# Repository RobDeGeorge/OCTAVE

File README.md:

<div align="center">

# OCTAVE

### **O**pen-source **C**ross-platform **T**elematics for **A**ugmented **V**ehicle **E**xperience

<sub>The real app, shot from a script: a real phone mirrored live (street names made up), engine data from the built-in car simulator.</sub>

**Windows · macOS · Linux · Raspberry Pi / Orange Pi · Android · your browser**

**Try it in your browser: https://robdegeorge.com/OCTAVE/** (the simulated car, no install, about 25 MB)

### [Download](https://github.com/RobDeGeorge/OCTAVE/releases/latest) &nbsp;·&nbsp; [Wiki](https://robdegeorge.com/OCTAVE/wiki/) &nbsp;·&nbsp; [Build your own frontend](https://robdegeorge.com/OCTAVE/wiki/writing-a-frontend.html) &nbsp;·&nbsp; [Frontend playground](https://robdegeorge.com/OCTAVE/playground.html)

</div>

---

**OCTAVE is a car head unit you build yourself**, on a Pi behind the dash, a laptop or an old Android tablet. Your phone, your music and the car's own data on one screen, and every pixel yours to change. I daily-drive it in my 2003 Jeep TJ.

> **Getting data from your car:** plug a $15–30 ELM327 OBD-II adapter into the port under your dash (every US car since 1996 has one). USB works everywhere; Bluetooth pairs inside OCTAVE on Linux and the Pi, and through system settings on Windows and macOS; BLE works on Android.
>
> No car handy? `octave --sim` drives a simulated one, in any build.

<table>
<tr>
<td width="33%" align="center"><br><b>Your phone on the dash</b><br><sub>Android by cable or Wi-Fi, iPhone over AirPlay</sub></td>
<td width="33%" align="center"><br><b>Music paints the dash</b><br><sub>Every song recolours the UI</sub></td>
<td width="33%" align="center"><br><b>A Home that is yours</b><br><sub>Pick one, or write your own</sub></td>
</tr>
<tr>
<td align="center"><br><b>A black box</b><br><sub>Every drive recorded</sub></td>
<td align="center"><br><b>Shift light & codes</b><br><sub>Read and clear the check-engine light</sub></td>
<td align="center"><br><b>Open API</b><br><sub>Drive it from a browser or a script</sub></td>
</tr>
<tr>
<td align="center"><br><b>Your car in 3D</b><br><sub>The Jeep, a BMW, or a model of your own</sub></td>
<td align="center"><br><b>Your own screen</b><br><sub>Swap the whole UI for one you wrote</sub></td>
<td align="center"><br><b>Its own hardware</b><br><sub>Designed here, not built yet</sub></td>
</tr>
</table>

---

## Your phone on the dash

Plug in an Android phone and it is on the dash: in the middle of Home, or in place of the album art. **Nothing to install on the phone**, only USB debugging turned on.

- **Pull the cable and it carries on** over Wi-Fi (Android 11+), song and all.
- **Touch it on the dash**, and the dash's play, skip and volume drive the phone's player.

**iPhone:** OCTAVE is an AirPlay receiver, and pairs as a Bluetooth mouse so taps on the dash reach the phone. Linux and the Pi for now.

**Android Auto** runs through Google's Desktop Head Unit or OCTAVE's own receiver (beta).

## Music that paints the whole dash

Every song recolours the whole interface from its cover. Tap the art to play it on something else: a spinning vinyl, or one of five 3D players, from a record player to an iPod. Local MP3, M4A and FLAC.

## A Home that is yours

<p align="center"><sub>Cockpit, Glass, Trail, Retro, Rings, Telemetry: the same car, the same minute.</sub></p>

Pick your Home in Settings: six screens built by hand, each its own idea of a dash, or the phone-in-the-middle one at the top of this page.

Or write your own. A dashboard is a small JSON file: a grid of **16 widget types** bound to any of **129 live readings** ([format](docs/GAUGE_AUTHORING.md)). Drop it in the dashboards folder and it appears. Or build it in a browser, previewed live on the car's screen:

Every reading your car reports is one tap away as plain cards, and every page re-flows for an upright screen.

<p align="center">
  
  &nbsp;

</p>

## A black box for every drive

OCTAVE records **every reading of every drive** in the background. Trip History charts any of them over a whole trip and exports CSV.

**Trends** compares your drives: warm-up time, coolant, voltage, idle, fuel trims. When recent drives drift it says so, and what usually causes it. Here a thermostat is starting to stick open.

<sub>The history in these pictures is generated: 40 drives with a thermostat wearing out.</sub>

## Shift light, warnings and trouble codes

Set your own RPM bands: green, flashing yellow, then **the whole screen strobes red**, whatever page you're on.

Check-engine light on? Read the codes in plain English and clear them from the dash.

## Your car, live in 3D

An inclinometer: your vehicle over a level ring, tilted in real time by an IMU on the dash. A rigged Jeep TJ and a BMW 330i ZHP ship with it, or add a model of your own car (any `.glb`, [guide](docs/VEHICLES.md)).

Pitch, roll, heading, G-force, altitude and temperature, sampled at 200 Hz.

## Drive it from anything

<table>
<tr>
<td width="38%" align="center"></td>
<td>

Everything the touch screen can do is open to other programs over a small JSON API. Start OCTAVE with `--service --service-bind 0.0.0.0` and open **`http://<head-unit-ip>:9876/`** on your phone, or run it with **no screen at all** (`--headless`) and make your own UI.

```python
from octave_client import Client

with Client() as octave:
    octave.call("nowPlaying", "next")
    octave.subscribe("paramStore", properties=["RPM", "SPEED"])
    for event in octave.events():
        print(event["values"])        # {'RPM': 2210, 'SPEED': 41}
```

[SDKs](sdk/) for Python, TypeScript and Go, [starter projects](templates/), the [API reference](https://robdegeorge.com/OCTAVE/wiki/api-reference.html), and a walkthrough: **[Writing a Frontend](https://robdegeorge.com/OCTAVE/wiki/writing-a-frontend.html)**. Install yours as the head unit's screen from Settings; five presses of mute always bring the built-in one back.

**[Try a frontend in your browser](https://robdegeorge.com/OCTAVE/playground.html)**, or browse the **[gallery](https://robdegeorge.com/OCTAVE/wiki/frontend-gallery.html)** of five complete examples (`examples/frontends/`, MIT).

</td>
</tr>
</table>

<p align="center"><sub>Glass (Svelte), Sunlight (Go), Retro Cluster (Rust), Arcade (C + SDL2), Console (Python): five complete screens for the same car.</sub></p>

## Hardware designed here

The $20 ELM327 clones work, and they are the slow part of the system. So OCTAVE is getting hardware of its own, designed in this repository as code: [`hardware/`](hardware/).

- **OBD adapter:** every OBD-II bus on one 80 x 55 mm board (two CAN, K-line, J1850 VPW / PWM for older cars like my TJ), an STM32 on the car's side, an ESP32 for Bluetooth and Wi-Fi, USB-C.
- **LoRa pod:** where the parked car is, beaconed over LoRa where there is no phone signal ([plan](TODO/lora-car-finder.md)).
- **Volume knob:** wireless, battery-powered, with a ring of twelve LEDs that follows the theme.

> **Where it stands:** all three boards are designed and routed. **Nobody else has reviewed them, and none has been ordered or built.** Read them, tell me what is wrong with them, but do not send them to a fab yet ([plan](TODO/diy-obd-adapter.md)). Nothing in OCTAVE depends on them.

---

## Install

Grab the file for your platform from **[Releases](https://github.com/RobDeGeorge/OCTAVE/releases/latest)**. No toolchain needed.

| Platform | File | |
|---|---|---|
| Windows | `OCTAVE-<version>-windows-x86_64.exe` | Run the installer |
| macOS | `OCTAVE-<version>-macos.dmg` | Drag to Applications |
| Linux | `OCTAVE-<version>-linux-x86_64.AppImage` | `chmod +x`, then run |
| Raspberry Pi / Orange Pi (64-bit) | `OCTAVE-<version>-linux-aarch64.AppImage` | `chmod +x`, then run |
| Android | `OCTAVE-<version>-android-arm64-v8a.apk` | Sideload it |

<details>
<summary>Platform notes</summary>

- **Linux:** Ubuntu 22.04+, Debian, Mint, Fedora, openSUSE and Arch. Arch may need `sudo pacman -S fuse2`, or run `./OCTAVE-*.AppImage --appimage-extract-and-run`.
- **Android:** releases from 0.9.4 on share one signing key and update in place. Coming from 0.9.3 or older, uninstall the old version first.

</details>

## How it compares

| | OCTAVE | Crankshaft | OpenAuto Pro | Stock Android Auto |
|---|---|---|---|---|
| Open source | Yes, GPLv3 | Yes | partial | No |
| Works without a phone | Yes | No, AA projection | No, AA projection | No |
| Live OBD-II, your own dashboards | Yes | No | limited | No |
| Records every drive | Yes | No | No | No |
| Phone mirroring | Yes: Android with nothing to install, iPhone over AirPlay | AA only | AA only | n/a |
| Open API for your own UI | Yes | No | No | No |
| Fully themable / forkable UI | Yes, QML | limited | limited | No |
| Develop on your laptop | Yes, Win / macOS / Linux | Pi only | Pi only | n/a |

## Everything else it does

- **Swipe between sections**: a sideways flick on any page opens the next one
- **ESP32 wireless volume knob** with an LED ring that matches the theme
- **Gesture sensor** (PAJ7620U2): wave to skip, pause or change the volume
- **Bluetooth OBD adapters** found, paired and connected from the app on Linux; BLE adapters on Android
- **Readings your car's maker kept to itself**: describe a manufacturer-specific PID in a file and it becomes a gauge like any other ([guide](docs/CUSTOM_PIDS.md))
- **A bus monitor**: watch and record the raw messages on the vehicle bus, listen only ([guide](docs/BUS_MONITOR.md))
- **Spotify** (experimental): your playlists in the same song table as your own music, playing on the Spotify app on your phone (Premium)
- **Pick the audio output**: the car's amp, a USB DAC or Bluetooth, from Settings
- **The browser demo is the real app**: point it at a folder of your own music, or connect a real adapter from Chrome or Edge, Bluetooth LE or on a USB cable
- **100+ settings**, all on the screen, all saved
- **The whole wiki inside the app**, readable offline
- **Logs and crash traces** you can export from the dash when something goes wrong

---

## Hack on it

OCTAVE is C++ / Qt 6 with a QML frontend, built with CMake, small enough to fork. `--dev` runs it with a **simulated car** (warm-up, overheating and low-fuel scenarios) and simulated motion, so you can work on gauges at your desk.

<details>
<summary><b>Build from source</b></summary>

Qt 6.7+ and CMake 3.21+:

```bash
git clone https://github.com/RobDeGeorge/OCTAVE.git
cd OCTAVE
cmake -S . -B build -DCMAKE_BUILD_TYPE=Debug
cmake --build build -j8
./build/octave --dev                       # with the simulated car
ctest --test-dir build --output-on-failure # the test suite
```

Every platform and packaging target is in [BUILD.md](BUILD.md). The optional Python tools around the app (dev scripts, docs builders) install into a virtualenv next to the checkout:

```bash
python3 -m venv venv && venv/bin/pip install -r requirements.txt
```

Until October 2026 OCTAVE also had a Python / PySide6 backend. It is frozen, with its own wiki, on the [`python-final`](https://github.com/RobDeGeorge/OCTAVE/tree/python-final) branch.

</details>

<details>
<summary><b>Dev tooling: how the clips above were made</b></summary>

Every clip and picture in this README is scripted, and one command makes them all again. `./build/octave --dev --profile` (a Debug build) runs OCTAVE with the simulator and a local command server; a story script drives it scene by scene (navigate, play, floor the throttle, tap buttons by their label, type into fields), captures the window from inside Qt, and writes WebP and PNG. The same run fills the black box with two months of mock drives, shoots the browser pages in headless Chromium, renders the boards with `kicad-cli` from the committed design, and then checks that every picture this file points at exists. The same channel is exposed as MCP tools, so a coding agent can drive the app, change settings, read performance counters and record clips. The in-app half is in `src/dev/`; see the [Development guide](https://robdegeorge.com/OCTAVE/wiki/development.html).

</details>

## What's next

- **The OBD adapter and the pods as real boards**: a review, a first order, and firmware on hardware ([plan](TODO/diy-obd-adapter.md))
- **Android on the Play Store**: the APK runs today as a sideload ([plan](TODO/android-cpp-port.md))
- **Wireless CarPlay / Android Auto** through a CarlinKit dongle ([plan](TODO/carlinkit-dongle-port.md))
- **Video over the API**, so your own frontend can show the phone mirror too ([plan](TODO/open-backend.md))

Every plan lives in [`TODO/`](TODO/).

## Documentation

The **[wiki](https://robdegeorge.com/OCTAVE/wiki/)** covers the architecture, every manager and page, every setting, hardware setup and the build guides. The same pages ship in [`wiki/`](wiki/index.html) and inside the app. Building gauges: [`docs/GAUGE_AUTHORING.md`](docs/GAUGE_AUTHORING.md). Building a frontend: [Writing a Frontend](https://robdegeorge.com/OCTAVE/wiki/writing-a-frontend.html) and [`docs/api/`](docs/api/README.md).

## Contributing

Pull requests and bug reports are welcome. Built a dashboard, a sensor integration, a port to new hardware, or your own frontend? Open an issue or a PR. I'd love to see it.

<details>
<summary><b>Built with</b></summary>

OCTAVE stands on a lot of other people's work.

**C++ app (every release binary)**

| Library | Used for |
|---|---|
| [Qt 6](https://www.qt.io/) (Core, Gui, Qml, Quick, Quick Controls 2, Multimedia, Network, Concurrent, SerialPort, Bluetooth) | The whole application: UI, audio playback, networking, serial and Bluetooth OBD |
| Qt Quick 3D, Quick 3D Asset Utils, Quick Timeline | The 3D Jeep and the music-device scenes |
| Qt DBus | BlueZ pairing on Linux |
| Qt Sensors | The phone's motion sensors on Android |
| [TagLib](https://taglib.org/) | Reading tags and embedded album art |
| [FFmpeg](https://ffmpeg.org/) (libavcodec, libavutil) | Decoding the phone mirror's H.264 stream |
| [SQLite](https://sqlite.org/) | The black box (compiled in from `third_party/sqlite/`) |
| [OpenSSL](https://www.openssl.org/) | The built-in Android Auto receiver's encryption; the AirPlay receiver |
| [libplist](https://libimobiledevice.org/) | The AirPlay receiver (Linux), with FFmpeg and OpenSSL |
| [CMake](https://cmake.org/) | Build system |

**Python helper tools (optional, `requirements.txt`)**

| Package | Used for |
|---|---|
| [MCP Python SDK](https://github.com/modelcontextprotocol/python-sdk), [Pillow](https://python-pillow.org/), [mss](https://github.com/BoboTiG/python-mss), [NumPy](https://numpy.org/), [psutil](https://github.com/giampaolo/psutil) | Dev tooling: MCP servers, screenshots and clips, perf scripts |
| [python-OBD](https://github.com/brendan-w/python-OBD) | Dev scripts for reading and clearing trouble codes |
| [Ruff](https://docs.astral.sh/ruff/) | Lint |

**Android**

| Library | Used for |
|---|---|
| Qt for Android, Gradle, Android SDK / NDK | Building the APK |
| [OpenSSL](https://www.openssl.org/) | HTTPS for Qt Network (`android/openssl/`) |

**Code bundled in this repository**

| Component | License | Where |
|---|---|---|
| [scrcpy](https://github.com/Genymobile/scrcpy) server, forked at v3.3.4 | Apache 2.0 | `phone_server/`, prebuilt jar in `tools/phone-server/` |
| [UxPlay](https://github.com/FDH2/UxPlay)'s AirPlay library, 1.74 | LGPL 2.1+, with GPL 3.0 and MIT parts (see its README) | `third_party/uxplay/` |
| [QR Code generator library](https://www.nayuki.io/page/qr-code-generator-library) by Project Nayuki | MIT | `src/phone_mirror/qrcodegen.*` |
| Android platform-tools (`adb`) | See its `NOTICE.txt` | `tools/platform-tools/` |

**External tools and services:** adb (phone mirroring and Android Auto), Google's Android Auto Desktop Head Unit (the Android Auto view).

**The boards (`hardware/`):** [KiCad](https://www.kicad.org/) (the project, `kicad-cli` checks, fab output and the renders above), [Freerouting](https://github.com/freerouting/freerouting) (autorouting), [ngspice](https://ngspice.sourceforge.io/) (simulations), `arm-none-eabi-gcc` (firmware).

**Fonts, icons and 3D assets**

- **[Google Sans](https://fonts.google.com/)**: UI typeface. **[JetBrains Mono](https://www.jetbrains.com/lp/mono/)**: monospace readouts.
- **OCTAVE Symbols**: a subset of [Noto Sans Symbols and Noto Sans Symbols 2](https://fonts.google.com/noto) (SIL OFL), renamed as the OFL requires, built by `tools/fonts/build_symbol_font.py` with [fontTools](https://github.com/fonttools/fonttools).
- **Icons**: original SVGs drawn for OCTAVE (Illustrator sources in `frontend/assets/-src/`).
- **The 2003 Jeep TJ**: an original model, built procedurally in [Blender](https://www.blender.org/) by `tools/vehicle/build_jeep_tj.py` from photos of one real TJ; no third-party meshes or textures ([details](tools/vehicle/README.md)).
- **Record player, cassette deck, CD player, iPod and friends**: original glTF models generated by `tools/music_devices/generate.py` (NumPy, Pillow).
- **Studio lighting (`.hdr`)**: generated by `tools/vehicle/build_studio_probe.py`.

**CI and packaging:** [GitHub Actions](https://github.com/features/actions) with [install-qt-action](https://github.com/jurplel/install-qt-action), [setup-android](https://github.com/android-actions/setup-android) and [action-gh-release](https://github.com/softprops/action-gh-release); [vcpkg](https://vcpkg.io/) and [Homebrew](https://brew.sh/) for TagLib and FFmpeg; [Inno Setup](https://jrsoftware.org/isinfo.php) for the Windows installer; [linuxdeploy](https://github.com/linuxdeploy/linuxdeploy) with its Qt plugin for the AppImages; `windeployqt`, `macdeployqt` and `androiddeployqt` from Qt.

</details>

## License

Copyright 2026 Rob DeGeorge.

OCTAVE is free software: you can redistribute it and/or modify it under the terms of the GNU General Public License as published by the Free Software Foundation, either version 3 of the License, or (at your option) any later version. It is distributed in the hope that it will be useful, but WITHOUT ANY WARRANTY; without even the implied warranty of MERCHANTABILITY or FITNESS FOR A PARTICULAR PURPOSE. See [LICENSE](LICENSE) for the full text.

The service clients (`sdk/`), starter projects (`templates/`) and example frontends (`examples/frontends/`) are MIT, so a frontend you build on them can use any license ([Your Frontend, Your License](wiki/writing-a-frontend.html#license)).

Code published before 2026-10-12 (v0.9.4 and earlier) was released under the MIT License and remains available under those terms.

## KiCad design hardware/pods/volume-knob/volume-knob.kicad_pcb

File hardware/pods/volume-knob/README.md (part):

# OCTAVE wireless volume knob, Rev 0

A battery-powered knob for OCTAVE's volume: an ESP32-C3, a rotary encoder with a push switch, a ring of 12 addressable RGB LEDs and a rechargeable cell on a 47 mm round board. It talks ESP-NOW to the ESP32-S3 USB dongle OCTAVE already supports (`src/managers/esp32volumemanager.cpp`: `+N` / `-N` / `M` lines one way, volume, mute and colour the other), so the app needs no change. It is an OCTAVE pod (`../README.md`) on the radio link. Built for a Jeep parked in Arizona: every part is rated to 80 C or more.

**Status:** generated, routed and checked by rule (ERC 0 errors, DRC 0 clearance errors, 0 unconnected, schematic and board agree), by two datasheet audits of the netlist, one review of the circuit and one of the routed layout, whose findings are fixed (see "What the reviews changed"). A third audit (five independent reviews against the makers' datasheets: pin numbers and land patterns, the power chain, the module and what firmware needs of it, the manufacturing files, the routed copper and the mechanics) found no wrong pin, footprint or rotation; what it changed is in the same section, and those last changes are themselves unreviewed. Not reviewed by a person, not ordered, no firmware. Read "Before ordering".

## What is on it

| Block | Part | Why this one |
|---|---|---|
| Cell | Nichicon SLB12400H1311CX, lithium titanate, 2.1 V 130 mAh, 12.5 x 40 mm | The only small rechargeable found that is rated for a hot car: -30 to 80 C, no thermal runaway, 20,000 cycles. A LiPo is rated to 60 C at best. Hand-fitted (not an LCSC part) |
| Charger | TI BQ25173-Q1, linear, set to 2.40 V and 150 mA | A charger whose voltage can be set under the cell's 2.5 V limit. About an hour for a full charge |
| Cut-off | TI TPS3840PL16 on the boost's enable | Stops the discharge at 1.6 V, back on at 1.7 V. The cell is rated to 1.5 V and rests at 1.98 V when empty, so only load on an empty cell trips it. The 1.8 V PL18 was the first choice: none in stock |
| 3.3 V | TI TPS61299 boost, 95 nA quiescent | The knob sleeps nearly all its life |
| Reset | TI TPS3840DL28 on the module's EN | The rail rises and falls slowly with the cell |
| MCU | ESP32-C3-MINI-1-H4X (105 C) | ESP-NOW, 5 uA deep sleep, flashes over its own USB |
| Encoder | Alps EC11J1525402, reflow mount, 30 detents, push switch | The 85 C encoder that leaves the back of the board flat for the cell |
| LEDs | 12 x WS2812B-2020-V6 behind a TPS22919 switch | The V6 runs from 3.3 V and draws under 1 uA dark |
| USB-C | HRO TYPE-C-31-M-12, USBLC6-2SC6 | Charging and flashing |

Top: the encoder in the centre, the LED ring at 14 mm radius, the encoder's pull-ups and filters in columns beside it and the cell's fuse; the ring's supply and data are wired by hand in `gen/prewire.py` (a supply ring inside the LEDs, the data chain outside). Bottom: the cell across the middle, wholly inside the outline at its largest tolerance (13 x 42 mm), every test pad, each LED's capacitor under its own LED (D10's is 7.5 mm away, the module is under that LED), the module above it with its antenna over a 16 mm notch cut in the rim, USB-C at the rim below with the charger on one side and the boost converter on the other. Four layers: signals, ground plane, signals, signals.

Expansion row: six plated holes (1.0 mm, 2.54 mm pitch, on an arc at the rim beside the USB socket) for wires, named on the top: GND (square pad), 3V3, IO8, IO9, IO2, IO21. The module has no unused pin, so these are the three strapping pins and the boot-log pin, free once it has started: IO8 and IO2 must not be held low at reset, IO9 low at reset is the ROM downloader, IO21 prints the boot log. Each of IO8, IO9 and IO2 has a 10k pull-up to 3V3 (IO8 and IO9 make an I2C bus as they are). 3V3 reaches its hole on 24 mm of 0.2 mm track: a sensor, not a motor. The holes follow the rim, so a straight 6-pin header does not fit them: wires, or two 3-pin headers (0.1 mm off, inside the holes' slack).

For the fun of it, on the top between the LED ring and the rim: the wizard of the terminal greeting (`gen/wizard.txt`, as on the OBD adapter, here 6.5 mm across: a cell is 0.13 mm, so it is a silhouette with no shading and its finest specks may not print), "One Ring to rule them all" round the lower right of the ring of LEDs, OCTAVE and Rev 0 either side of the antenna notch, in Uncial Antiqua (SIL Open Font License). The font is not in the repo: `gen/mkart.py <font.ttf>` wrote the letters' outlines to `gen/art.json` once; `gen/art.py` says where each goes and bends it round the centre.

Pins: GPIO0 encoder A (wake), 1 encoder B (wake), 3 switch (wake), 4 cell voltage (ADC), 5 USB present (wake), 6 LED data, 7 charger /CE, 10 LED rail enable, 20 charger STAT, 18 / 19 USB, 2 / 8 / 9 strapping (pulled up; 9 is BOOT), 21 boot log on a test pad.

## Files

| Path | What |
|---|---|
| `gen/knob.py` | **The design.** Every part, its LCSC number, its pin-to-net map, and the notes on why. Edit this, not the KiCad files |
| `gen/parts.py` | LCSC part numbers, checked against JLCPCB's library on 2026-11-22 |
| `gen/libdefs.py` | Symbols KiCad does not ship (the module, the charger, the boost, the supervisors, the load switch) |
| `gen/layout.py` | Placement: fixed positions for what matters, a packer for the rest |
| `gen/prewire.py` | Copper laid by hand before the autorouter: the boost converter's loops, the cell's feed, the module's ground |
| `gen/routing.json` | The routed copper, frozen. `build.py route` replays it |
| `gen/jlc_corr.py` | Rotation / offset of each part in JLCPCB's placement file, fitted to JLCPCB's own footprints, and the rule for bottom-side parts |
| `gen/art.py`, `gen/art.json`, `gen/wizard.txt`, `gen/mkart.py` | The wizard, the quote and the name on the top silkscreen |
| `gen/mk3d.py` | Plain 3D shapes for the cell with its bent leads, the module, the encoder and the LEDs (for the renders only); every part but the test pads, fiducials and holes has a body |
| `gen/build.py` | Regenerates everything (below) |
| `lib/OCTAVE.pretty` | Footprints drawn from the makers' land patterns: the module, the encoder, the boost's WCSP, the cell |
| `volume-knob.kicad_sch` / `.kicad_pcb` | Generated KiCad 10 project |
| `fab/` | Generated: Gerber zip, JLCPCB BOM and CPL, the hand-fit list |
| `renders/` | Generated pictures of the board |

```bash
cd hardware/pods/volume-knob/gen
python3 build.py sch      # symbols, schematic, ERC
python3 build.py pcb      # board with placement
python3 build.py route    # replays gen/routing.json, pours, DRC
python3 build.py fab      # Gerbers, drill, BOM, CPL, renders
python3 build.py all
```

Use the system `python3` (KiCad's `pcbnew` module lives there). To route again after moving parts: `KNOB_REROUTE=1 python3 build.py route` (Freerouting 2.5, about 5 minutes; `FREEROUTING_JAR` to point at the jar). It lays the hand copper and a via for every ground pad, runs Freerouting on the signals, finishes any leftover with the grid router (`maze.py`), stitches the ground pours and freezes the result. Freerouting does not give the same answer twice: check `drc.rpt` after every fresh route.

## What DRC still says

- **NPTH inside courtyard (2):** the encoder's centre boss and locating pin come through the board under the cell. They stop 0.4 mm short of the far side of a 1.6 mm board. Do not order it thinner.
- **Footprint does not match library (6):** silkscreen that reached over the board edge was removed on the board, and the boost converter's lands have a smaller mask margin.

The board is 47 mm because that is the smallest disc that holds the cell at its tolerance with the module's antenna at the rim. Only 0402 parts sit under the cell's flanks (0.55 mm tall, 1.2 mm of air), nothing under its centre line.

## What the reviews changed

- **Circuit review:** the cut-off raised from 1.6 V to 2.0 V with a filtered supply; a reset supervisor on the module's EN; the USB ESD array's rail taken off VBUS; the USB-present divider changed so 4.4 V reads as a high; a fuse at the cell; the charge current lowered to 150 mA; a pull-down on the LED data line.
- **Layout review:** the boost's output capacitor now returns to the converter's one ground ball (it had been wired to the VSEL ball beside it); no via within 0.15 mm of any solder pad; no copper on any layer beside or under the antenna, rim to rim; 3.3 V goes from the boost to the module on a 1 mm trunk with two vias at each end; no pour under the screw heads or under the boost converter; fiducials on both sides; names at the test pads where there was room.
- **Second layout review and a manufacturing review (of the 47 mm board):** the cut-off lowered from 2.0 V to 1.8 V (2.0 V is inside the flat bottom of the cell's curve: radio activity could trip it from 10 to 30 % charge, and it would stay off until charged); two ground vias that cut into the USB shell's slots removed; the cell-voltage track that ran under the USB shell moved to an inner layer; the ground via in C21's pad removed (C8 shares C7's); a supply via of their own for the capacitors of D2 and D6; no drill map in the gerber zip. Footprints, pin numbering, the placement file's rotation rule, the boost's loop, the ground plane and the antenna strip were checked and found right.
- **Third audit (five reviews against the datasheets):** no wrong pin number, land pattern, LCSC number or placement rotation. Changed: the encoder's filter capacitors from 2.2 nF to 220 pF (with the 1M pull-up an opening contact took 3 ms to read high, as long as the wake from deep sleep, and the direction of the first click hangs on reading B before the detent); the switch's pull-up from 100k to 33k (Alps' minimum current for the switch is 0.1 mA); the cell-voltage resistor from 1M to 470k (pin leakage through 1M was up to 50 mV of error against a 70 mV-wide guard); the cut-off to the 1.6 V part (the 1.8 V one has no stock at JLCPCB); the board cut away under and beside the antenna (Espressif's rule when the antenna does not overhang the edge); the encoder's locating hole from a 1.6 x 1.9 mm slot to a 1.9 mm round hole (JLCPCB wants a slot twice as long as wide).
- **Left after the third audit, knowingly:**
  - The USB socket's mouth is level with the rim (HRO draws it 0.5 mm proud). A plug seats on the bare board; the housing needs an open pocket for the plug's overmould (13 x 7 mm) down to the board, no wall in front of the socket. Moving the socket out means routing USB again.
  - BOOST_EN runs on the second inner layer for 1 mm under the boost converter's balls and the corner of the inductor's pad. The converter's output loop still has ground under it.
  - The charger's branch of VBAT is 0.2 mm wide; the 3 A fuse does not protect it against a short at the charger. Normal current there is 150 mA.
  - CHG_STAT is on U0RXD with no pad: there is no UART download path, only USB. Whether the ROM downloader minds that line low (a full cell on USB) is not known; hold GPIO20 low on a dev board and run esptool over USB to find out.
  - Silkscreen names are 0.8 mm high with 0.12 mm strokes, under JLCPCB's stated 1.0 / 0.15: they may print faint.
  - IO2's track runs beside LED_DATA for 7 to 10 mm: not for an analogue input while the LEDs are being written.
- **Left after the earlier reviews, knowingly:**
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
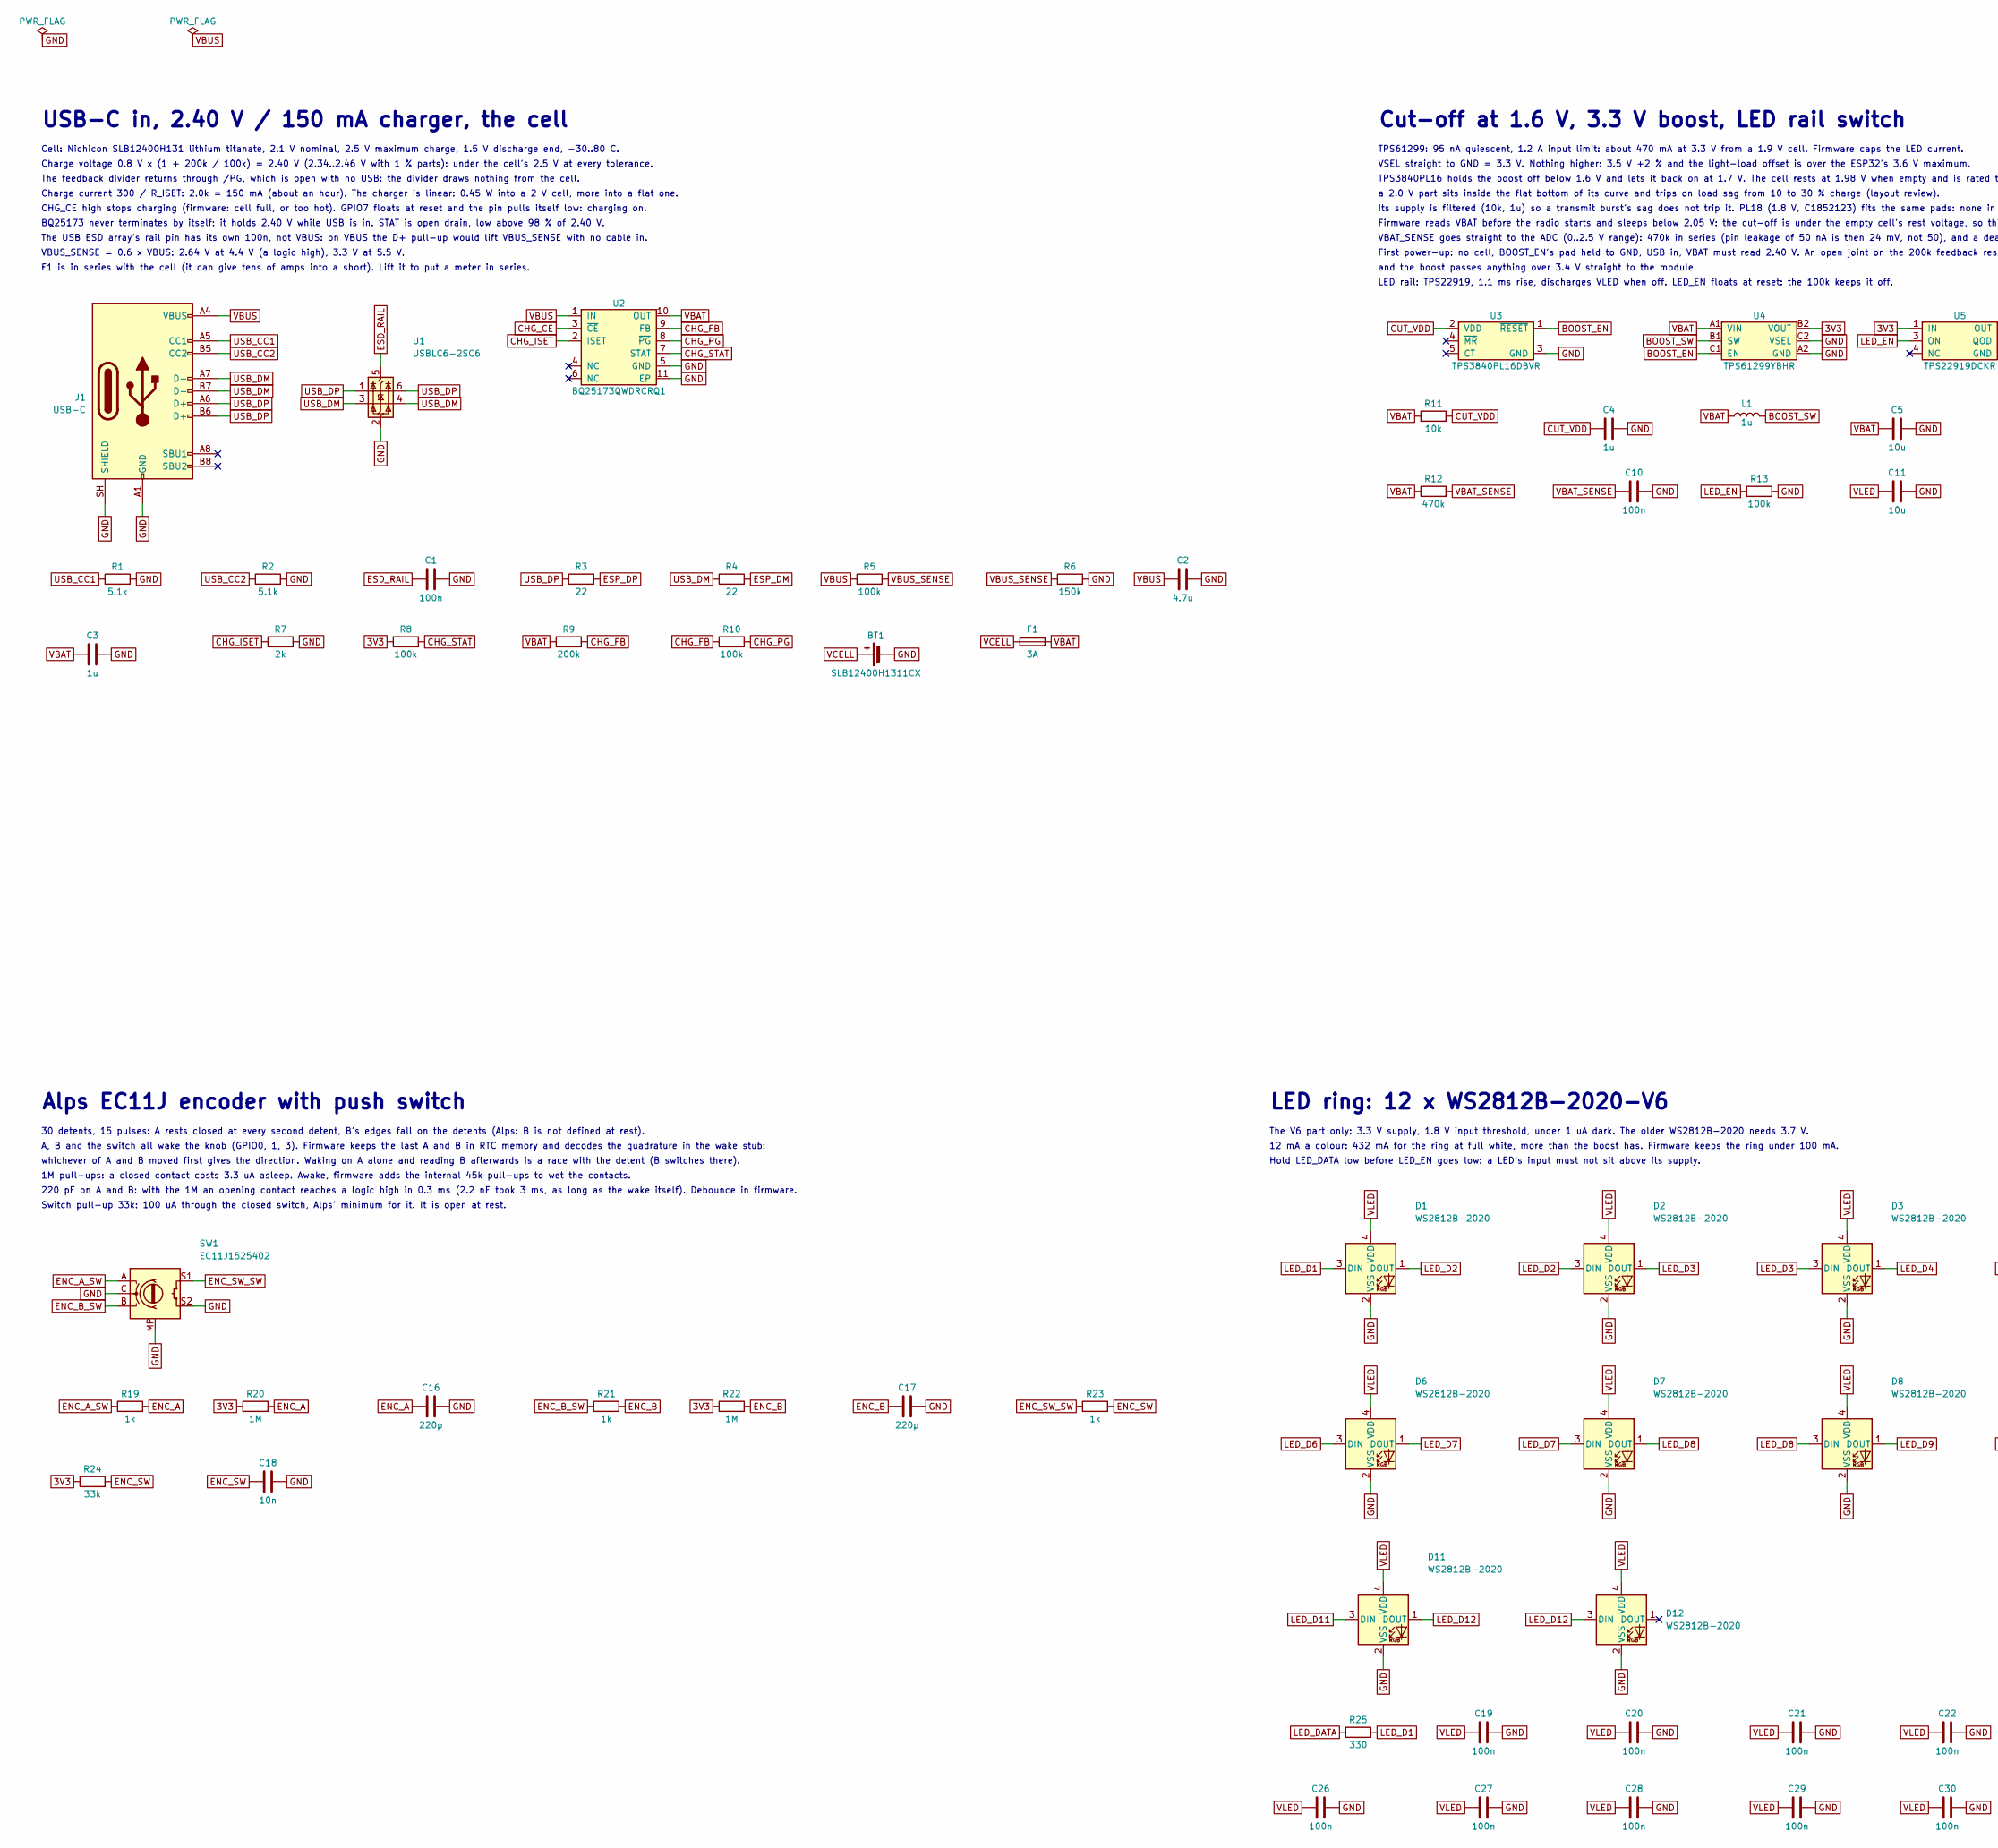
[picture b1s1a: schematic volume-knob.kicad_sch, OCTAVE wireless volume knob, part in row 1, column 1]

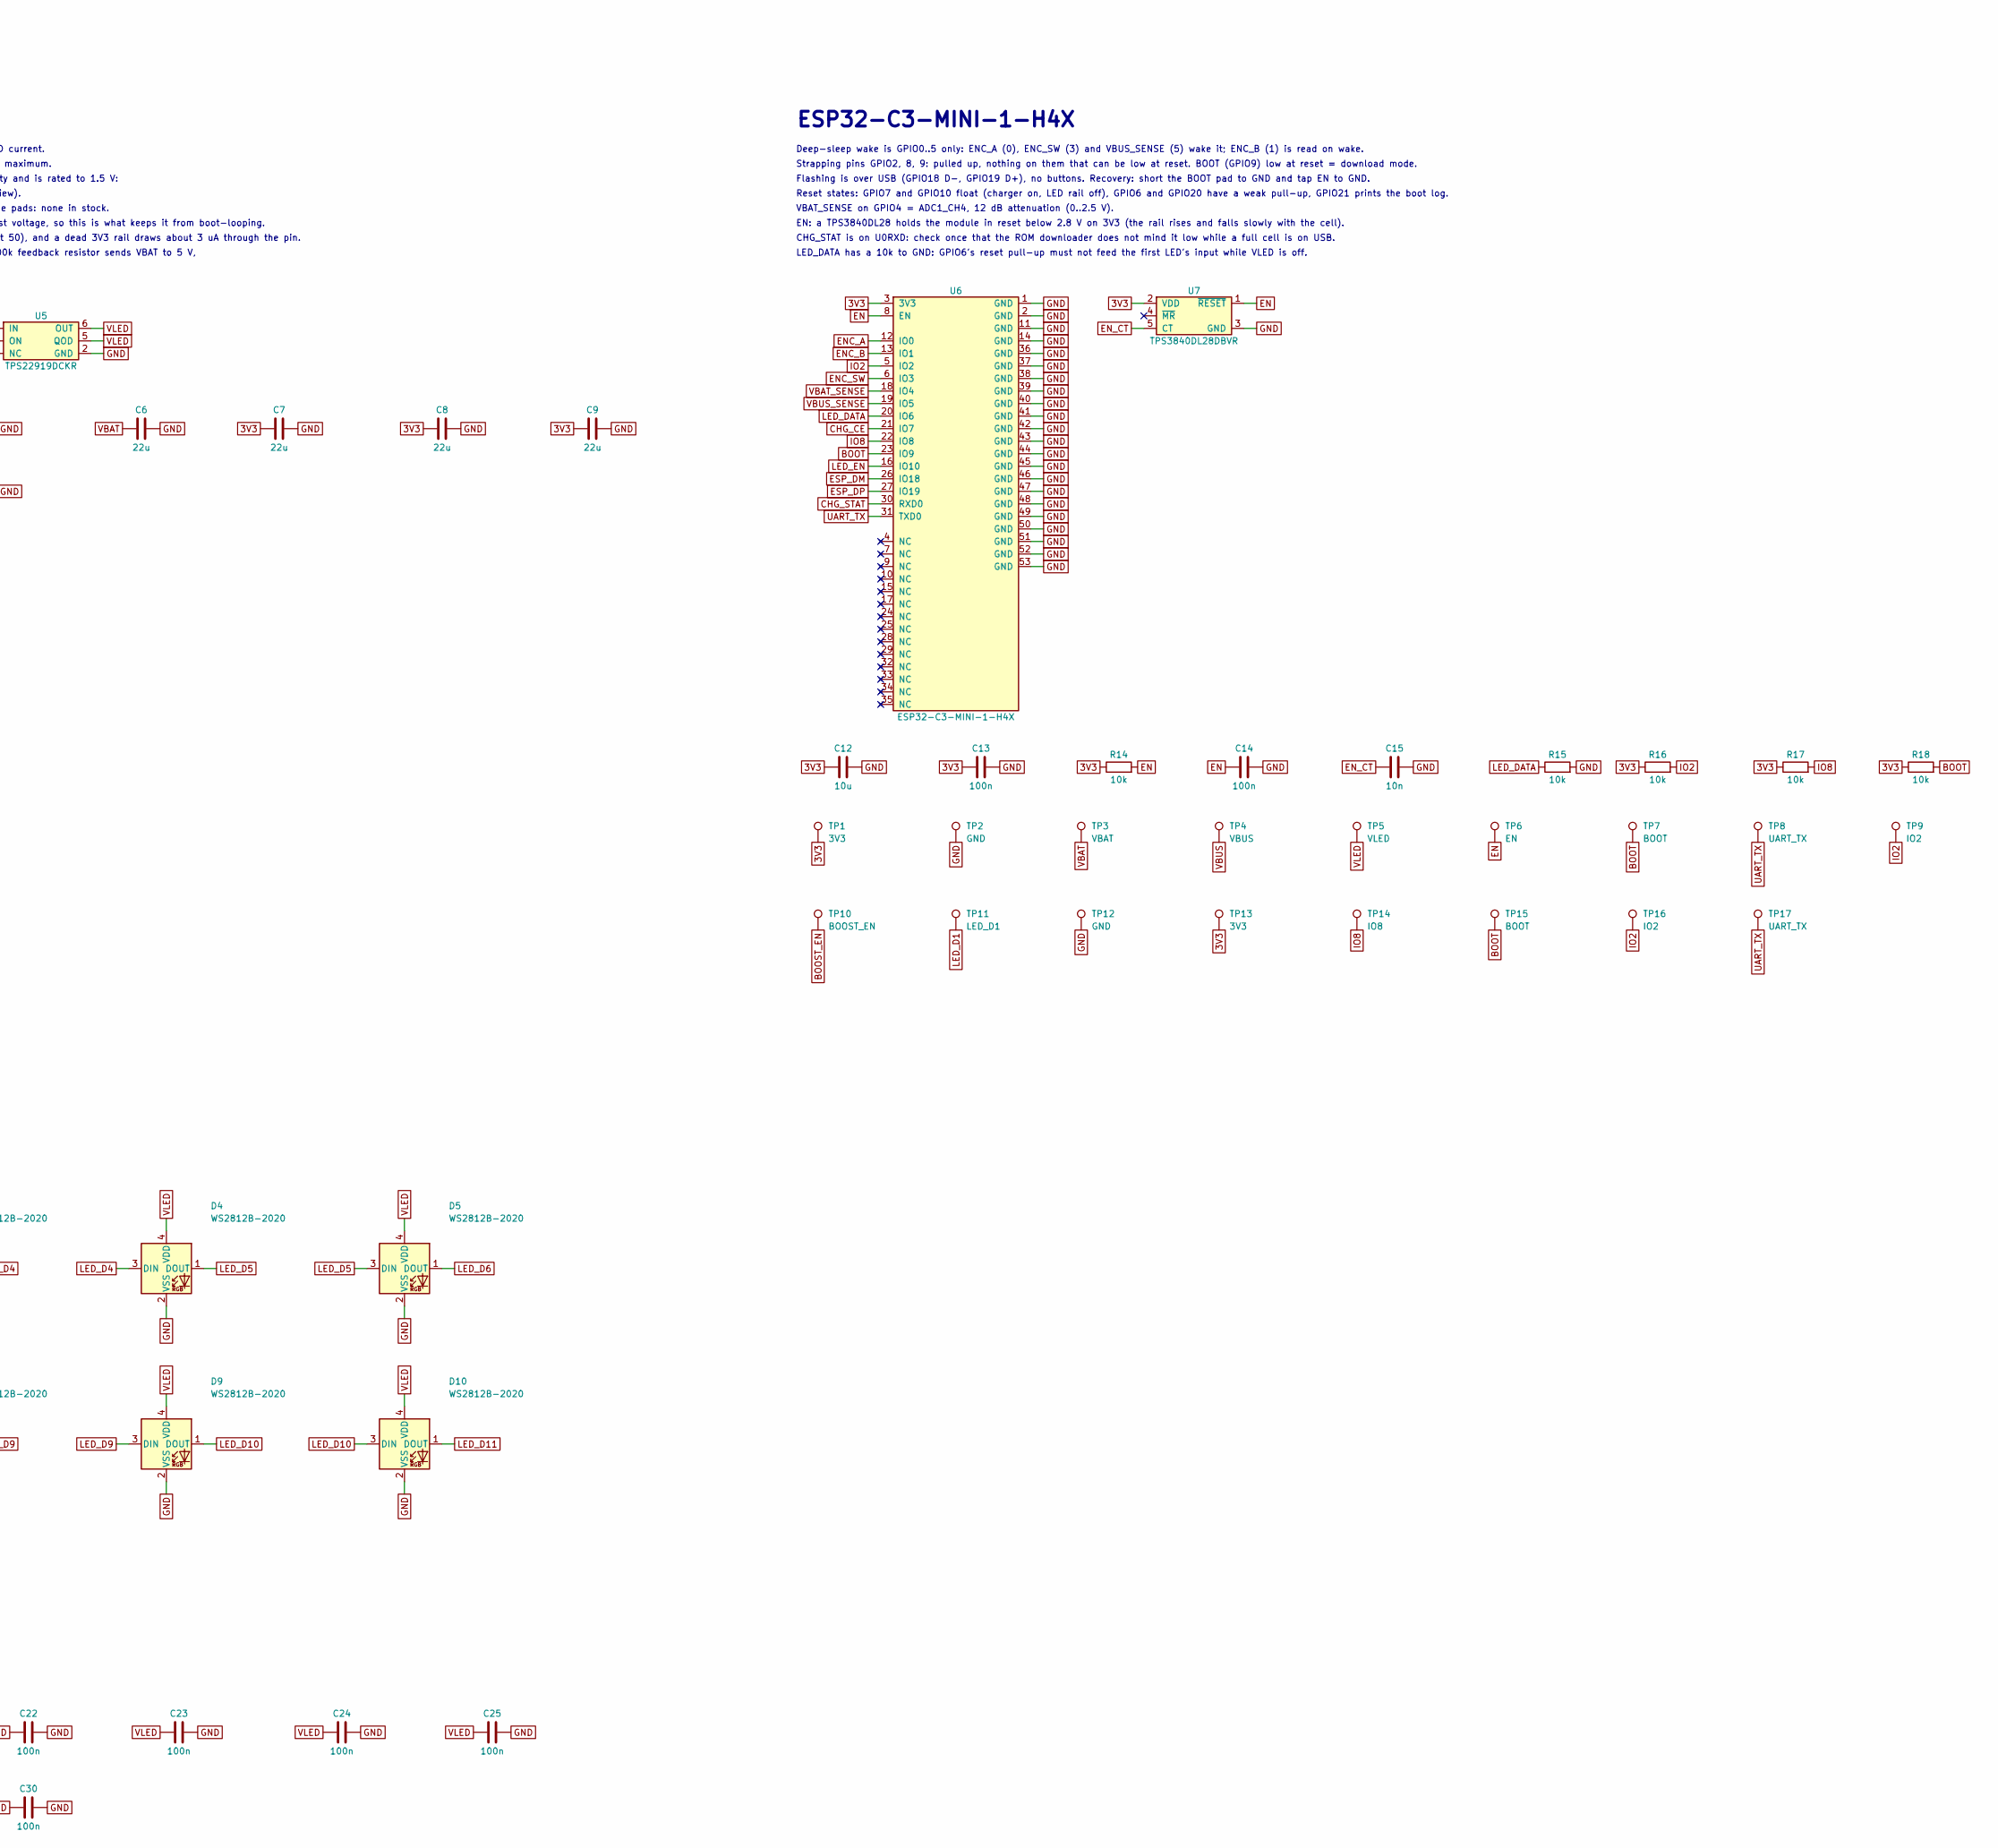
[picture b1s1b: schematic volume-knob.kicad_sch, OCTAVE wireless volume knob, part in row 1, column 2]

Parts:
BT1: SLB12400H1311CX; Battery_Nichicon_SLB12400_Horizontal; MPN SLB12400H1311CX
C1, C10, C13, C14, C19, C20, C21, C22, C23, C24, C25, C26, C27, C28, C29, C30: 100n; C_0402_1005Metric; LCSC C1525
C2: 4.7u; C_0805_2012Metric; LCSC C1779
C3, C4: 1u; C_0402_1005Metric; LCSC C52923
C5, C11, C12: 10u; C_0603_1608Metric; LCSC C19702
C6, C7, C8, C9: 22u; C_0805_2012Metric; LCSC C45783
C15, C18: 10n; C_0402_1005Metric; LCSC C15195
C16, C17: 220p; C_0402_1005Metric; LCSC C1530
D1, D2, D3, D4, D5, D6, D7, D8, D9, D10, D11, D12: WS2812B-2020; LED_WS2812B-2020_PLCC4_2.0x2.0mm; LCSC C52917434
F1: 3A; Fuse_0603_1608Metric; MPN 0467003.NRHF; LCSC C99558
J1: USB-C; USB_C_Receptacle_HRO_TYPE-C-31-M-12; LCSC C165948
L1: 1u; L_Sunlord_SWPA252012S; MPN WPN252012H1R0MT; LCSC C98348
R1, R2: 5.1k; R_0402_1005Metric; LCSC C25905
R3, R4: 22; R_0402_1005Metric; LCSC C25092
R5, R8, R10, R13: 100k; R_0402_1005Metric; LCSC C25741
R6: 150k; R_0402_1005Metric; LCSC C25755
R7: 2k; R_0402_1005Metric; LCSC C4109
R9: 200k; R_0402_1005Metric; LCSC C25764
R11, R14, R15, R16, R17, R18: 10k; R_0402_1005Metric; LCSC C25744
R12: 470k; R_0402_1005Metric; LCSC C25790
R19, R21, R23: 1k; R_0402_1005Metric; LCSC C11702
R20, R22: 1M; R_0402_1005Metric; LCSC C26083
R24: 33k; R_0402_1005Metric; LCSC C25779
R25: 330; R_0402_1005Metric; LCSC C25104
SW1: EC11J1525402; RotaryEncoder_Alps_EC11J15_SMD; LCSC C209762
TP1: 3V3; TestPoint_Pad_D1.0mm
TP2: GND; TestPoint_Pad_D1.0mm
TP3: VBAT; TestPoint_Pad_D1.0mm
TP4: VBUS; TestPoint_Pad_D1.0mm
TP5: VLED; TestPoint_Pad_D1.0mm
TP6: EN; TestPoint_Pad_D1.0mm
TP7: BOOT; TestPoint_Pad_D1.0mm
TP8: UART_TX; TestPoint_Pad_D1.0mm
TP9: IO2; TestPoint_Pad_D1.0mm
TP10: BOOST_EN; TestPoint_Pad_D1.0mm
TP11: LED_D1; TestPoint_Pad_D1.0mm
TP12: GND; IO_Hole_D1.7mm_Drill1.0mm_Square
TP13: 3V3; IO_Hole_D1.7mm_Drill1.0mm
TP14: IO8; IO_Hole_D1.7mm_Drill1.0mm
TP15: BOOT; IO_Hole_D1.7mm_Drill1.0mm
TP16: IO2; IO_Hole_D1.7mm_Drill1.0mm
TP17: UART_TX; IO_Hole_D1.7mm_Drill1.0mm
U1: USBLC6-2SC6; SOT-23-6; LCSC C7519
U2: BQ25173QWDRCRQ1; Texas_DRC0010J_ThermalVias; LCSC C20345235
U3: TPS3840PL16DBVR; SOT-23-5; LCSC C1852124
U4: TPS61299YBHR; TI_YBH0006_WCSP-6_0.8x1.2mm; LCSC C20882919
U5: TPS22919DCKR; SOT-363_SC-70-6; LCSC C2149796
U6: ESP32-C3-MINI-1-H4X; ESP32-C3-MINI-1; LCSC C41349510
U7: TPS3840DL28DBVR; SOT-23-5; LCSC C2066416

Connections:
3V3: C7.1, C8.1, C9.1, C12.1, C13.1, R8.1, R14.1, R16.1, R17.1, R18.1, R20.1, R22.1, R24.1, TP1.1, TP13.1, U4.B2 (VOUT), U5.1 (IN), U6.3 (3V3), U7.2 (VDD)
BOOST_EN: TP10.1, U3.1 (~RESET), U4.C1 (EN)
BOOST_SW: L1.2, U4.B1 (SW)
BOOT: R18.2, TP7.1, TP15.1, U6.23 (IO9)
CHG_CE: U2.3 (~CE), U6.21 (IO7)
CHG_FB: R9.2, R10.1, U2.9 (FB)
CHG_ISET: R7.1, U2.2 (ISET)
CHG_PG: R10.2, U2.8 (~PG)
CHG_STAT: R8.2, U2.7 (STAT), U6.30 (RXD0)
CUT_VDD: C4.1, R11.2, U3.2 (VDD)
EN: C14.1, R14.2, TP6.1, U6.8 (EN), U7.1 (~RESET)
ENC_A: C16.1, R19.2, R20.2, U6.12 (IO0)
ENC_A_SW: R19.1, SW1.A
ENC_B: C17.1, R21.2, R22.2, U6.13 (IO1)
ENC_B_SW: R21.1, SW1.B
ENC_SW: C18.1, R23.2, R24.2, U6.6 (IO3)
ENC_SW_SW: R23.1, SW1.S1
EN_CT: C15.1, U7.5 (CT)
ESD_RAIL: C1.1, U1.5 (VBUS)
ESP_DM: R4.2, U6.26 (IO18)
ESP_DP: R3.2, U6.27 (IO19)
GND: BT1.2 (-), C1.2, C2.2, C3.2, C4.2, C5.2, C6.2, C7.2, C8.2, C9.2, C10.2, C11.2, C12.2, C13.2, C14.2, C15.2, C16.2, C17.2, C18.2, C19.2, C20.2, C21.2, C22.2, C23.2, C24.2, C25.2, C26.2, C27.2, C28.2, C29.2, C30.2, D1.2 (VSS), D2.2 (VSS), D3.2 (VSS), D4.2 (VSS), D5.2 (VSS), D6.2 (VSS), D7.2 (VSS), D8.2 (VSS), D9.2 (VSS), D10.2 (VSS), D11.2 (VSS), D12.2 (VSS), J1.A1 (GND), J1.A12 (GND), J1.B1 (GND), J1.B12 (GND), J1.SH (SHIELD), R1.2, R2.2, R6.2, R7.2, R13.2, R15.2, SW1.C, SW1.MP, SW1.S2, TP2.1, TP12.1, U1.2 (GND), U2.5 (GND), U2.11 (EP), U3.3 (GND), U4.A2 (GND), U4.C2 (VSEL), U5.2 (GND), U6.1 (GND), U6.2 (GND), U6.11 (GND), U6.14 (GND), U6.36 (GND), U6.37 (GND), U6.38 (GND), U6.39 (GND), U6.40 (GND), U6.41 (GND), U6.42 (GND), U6.43 (GND), U6.44 (GND), U6.45 (GND), U6.46 (GND), U6.47 (GND), U6.48 (GND), U6.49 (GND), U6.50 (GND), U6.51 (GND), U6.52 (GND), U6.53 (GND), U7.3 (GND)
IO2: R16.2, TP9.1, TP16.1, U6.5 (IO2)
IO8: R17.2, TP14.1, U6.22 (IO8)
LED_D1: D1.3 (DIN), R25.2, TP11.1
LED_D2: D1.1 (DOUT), D2.3 (DIN)
LED_D3: D2.1 (DOUT), D3.3 (DIN)
LED_D4: D3.1 (DOUT), D4.3 (DIN)
LED_D5: D4.1 (DOUT), D5.3 (DIN)
LED_D6: D5.1 (DOUT), D6.3 (DIN)
LED_D7: D6.1 (DOUT), D7.3 (DIN)
LED_D8: D7.1 (DOUT), D8.3 (DIN)
LED_D9: D8.1 (DOUT), D9.3 (DIN)
LED_D10: D9.1 (DOUT), D10.3 (DIN)
LED_D11: D10.1 (DOUT), D11.3 (DIN)
LED_D12: D11.1 (DOUT), D12.3 (DIN)
LED_DATA: R15.1, R25.1, U6.20 (IO6)
LED_EN: R13.1, U5.3 (ON), U6.16 (IO10)
UART_TX: TP8.1, TP17.1, U6.31 (TXD0)
USB_CC1: J1.A5 (CC1), R1.1
USB_CC2: J1.B5 (CC2), R2.1
USB_DM: J1.A7 (D-), J1.B7 (D-), R4.1, U1.3 (I/O2), U1.4 (I/O2)
USB_DP: J1.A6 (D+), J1.B6 (D+), R3.1, U1.1 (I/O1), U1.6 (I/O1)
VBAT: C3.1, C5.1, C6.1, F1.2, L1.1, R9.1, R11.1, R12.1, TP3.1, U2.10 (OUT), U4.A1 (VIN)
VBAT_SENSE: C10.1, R12.2, U6.18 (IO4)
VBUS: C2.1, J1.A4 (VBUS), J1.A9 (VBUS), J1.B4 (VBUS), J1.B9 (VBUS), R5.1, TP4.1, U2.1 (IN)
VBUS_SENSE: R5.2, R6.1, U6.19 (IO5)
VCELL: BT1.1 (+), F1.1
VLED: C11.1, C19.1, C20.1, C21.1, C22.1, C23.1, C24.1, C25.1, C26.1, C27.1, C28.1, C29.1, C30.1, D1.4 (VDD), D2.4 (VDD), D3.4 (VDD), D4.4 (VDD), D5.4 (VDD), D6.4 (VDD), D7.4 (VDD), D8.4 (VDD), D9.4 (VDD), D10.4 (VDD), D11.4 (VDD), D12.4 (VDD), TP5.1, U5.5 (QOD), U5.6 (OUT)

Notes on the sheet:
USB-C in, 2.40 V / 150 mA charger, the cell
Cell: Nichicon SLB12400H131 lithium titanate, 2.1 V nominal, 2.5 V maximum charge, 1.5 V discharge end, -30..80 C.
Charge voltage 0.8 V x (1 + 200k / 100k) = 2.40 V (2.34..2.46 V with 1 % parts): under the cell's 2.5 V at every tolerance.
The feedback divider returns through /PG, which is open with no USB: the divider draws nothing from the cell.
Charge current 300 / R_ISET: 2.0k = 150 mA (about an hour). The charger is linear: 0.45 W into a 2 V cell, more into a flat one.
CHG_CE high stops charging (firmware: cell full, or too hot). GPIO7 floats at reset and the pin pulls itself low: charging on.
BQ25173 never terminates by itself: it holds 2.40 V while USB is in. STAT is open drain, low above 98 % of 2.40 V.
The USB ESD array's rail pin has its own 100n, not VBUS: on VBUS the D+ pull-up would lift VBUS_SENSE with no cable in.
VBUS_SENSE = 0.6 x VBUS: 2.64 V at 4.4 V (a logic high), 3.3 V at 5.5 V.
F1 is in series with the cell (it can give tens of amps into a short). Lift it to put a meter in series.
Cut-off at 1.6 V, 3.3 V boost, LED rail switch
TPS61299: 95 nA quiescent, 1.2 A input limit: about 470 mA at 3.3 V from a 1.9 V cell. Firmware caps the LED current.
VSEL straight to GND = 3.3 V. Nothing higher: 3.5 V +2 % and the light-load offset is over the ESP32's 3.6 V maximum.
TPS3840PL16 holds the boost off below 1.6 V and lets it back on at 1.7 V. The cell rests at 1.98 V when empty and is rated to 1.5 V:
a 2.0 V part sits inside the flat bottom of its curve and trips on load sag from 10 to 30 % charge (layout review).
Its supply is filtered (10k, 1u) so a transmit burst's sag does not trip it. PL18 (1.8 V, C1852123) fits the same pads: none in stock.
Firmware reads VBAT before the radio starts and sleeps below 2.05 V: the cut-off is under the empty cell's rest voltage, so this is what keeps it from boot-looping.
VBAT_SENSE goes straight to the ADC (0..2.5 V range): 470k in series (pin leakage of 50 nA is then 24 mV, not 50), and a dead 3V3 rail draws about 3 uA through the pin.
First power-up: no cell, BOOST_EN's pad held to GND, USB in, VBAT must read 2.40 V. An open joint on the 200k feedback resistor sends VBAT to 5 V,
and the boost passes anything over 3.4 V straight to the module.
LED rail: TPS22919, 1.1 ms rise, discharges VLED when off. LED_EN floats at reset: the 100k keeps it off.
ESP32-C3-MINI-1-H4X
Deep-sleep wake is GPIO0..5 only: ENC_A (0), ENC_SW (3) and VBUS_SENSE (5) wake it; ENC_B (1) is read on wake.
Strapping pins GPIO2, 8, 9: pulled up, nothing on them that can be low at reset. BOOT (GPIO9) low at reset = download mode.
Flashing is over USB (GPIO18 D-, GPIO19 D+), no buttons. Recovery: short the BOOT pad to GND and tap EN to GND.
Reset states: GPIO7 and GPIO10 float (charger on, LED rail off), GPIO6 and GPIO20 have a weak pull-up, GPIO21 prints the boot log.
VBAT_SENSE on GPIO4 = ADC1_CH4, 12 dB attenuation (0..2.5 V).
EN: a TPS3840DL28 holds the module in reset below 2.8 V on 3V3 (the rail rises and falls slowly with the cell).
CHG_STAT is on U0RXD: check once that the ROM downloader does not mind it low while a full cell is on USB.
LED_DATA has a 10k to GND: GPIO6's reset pull-up must not feed the first LED's input while VLED is off.
Alps EC11J encoder with push switch
30 detents, 15 pulses: A rests closed at every second detent, B's edges fall on the detents (Alps: B is not defined at rest).
A, B and the switch all wake the knob (GPIO0, 1, 3). Firmware keeps the last A and B in RTC memory and decodes the quadrature in the wake stub:
whichever of A and B moved first gives the direction. Waking on A alone and reading B afterwards is a race with the detent (B switches there).
1M pull-ups: a closed contact costs 3.3 uA asleep. Awake, firmware adds the internal 45k pull-ups to wet the contacts.
220 pF on A and B: with the 1M an opening contact reaches a logic high in 0.3 ms (2.2 nF took 3 ms, as long as the wake itself). Debounce in firmware.
Switch pull-up 33k: 100 uA through the closed switch, Alps' minimum for it. It is open at rest.
LED ring: 12 x WS2812B-2020-V6
The V6 part only: 3.3 V supply, 1.8 V input threshold, under 1 uA dark. The older WS2812B-2020 needs 3.7 V.
12 mA a colour: 432 mA for the ring at full white, more than the boost has. Firmware keeps the ring under 100 mA.

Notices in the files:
README.md:
License: GPL v3+
